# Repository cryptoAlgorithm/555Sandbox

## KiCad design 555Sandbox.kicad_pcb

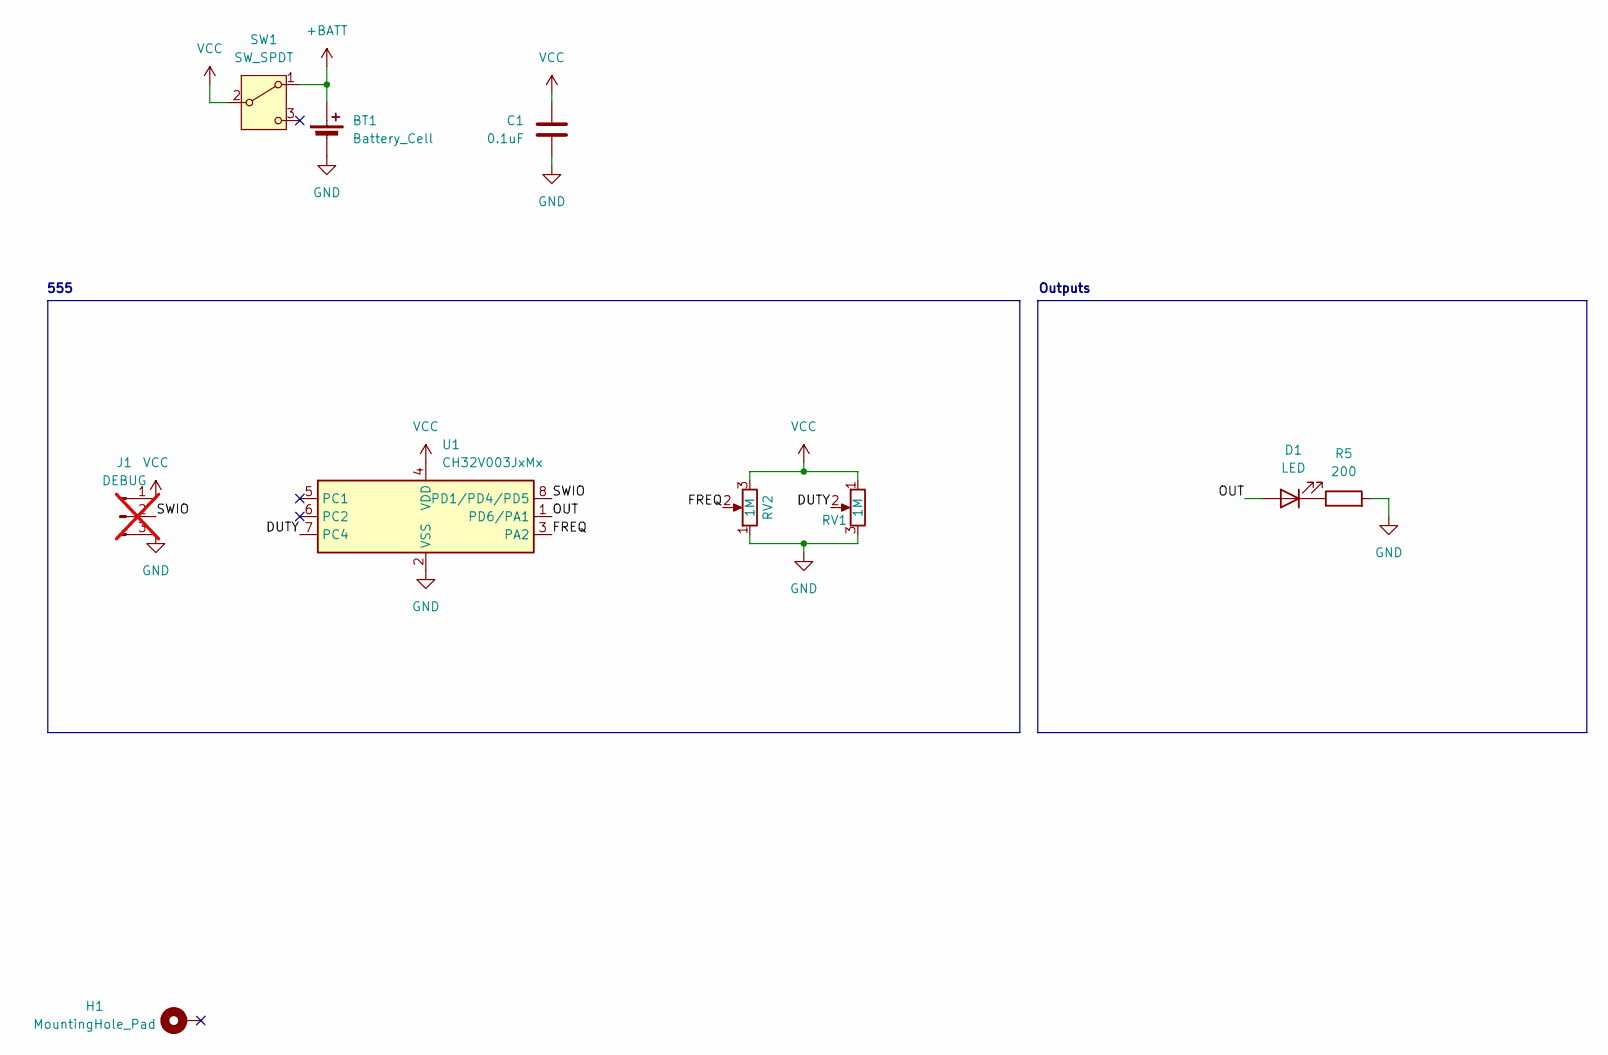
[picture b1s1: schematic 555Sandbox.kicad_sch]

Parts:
BT1: Battery_Cell; BatteryHolder_Keystone_3000_1x12mm; Part C238097
C1: 0.1uF; C_0603_1608Metric; Part C14663
D1: LED; LED_PLCC_2835; Part C7371920
H1: MountingHole_Pad; MountingHole_3mm_Pad
J1: DEBUG; PinHeader_1x03_P1.27mm_Vertical; not fitted
R5: 200; R_0603_1608Metric; Part C8218
RV1, RV2: 1M; Potentiometer_Runtron_RM-065_Vertical
SW1: SW_SPDT; SW_Slide_SPDT_Angled_CK_OS102011MA1Q
U1: CH32V003JxMx; SOP-8_3.9x4.9mm_P1.27mm; Part C5346354

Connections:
+BATT: BT1.1 (+), SW1.1 (A)
/DUTY: RV1.2, U1.7 (PC4)
/FREQ: RV2.2, U1.3 (PA2)
/OUT: D1.2 (A), U1.1 (PD6/PA1)
/SWIO: J1.2, U1.8 (PD1/PD4/PD5)
GND: BT1.2 (-), C1.2, J1.3, R5.2, RV1.3, RV2.1, U1.2 (VSS)
unnamed: D1.1 (K), R5.1
VCC: C1.1, J1.1, RV1.1, RV2.3, SW1.2 (B), U1.4 (VDD)

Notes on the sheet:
Outputs
555

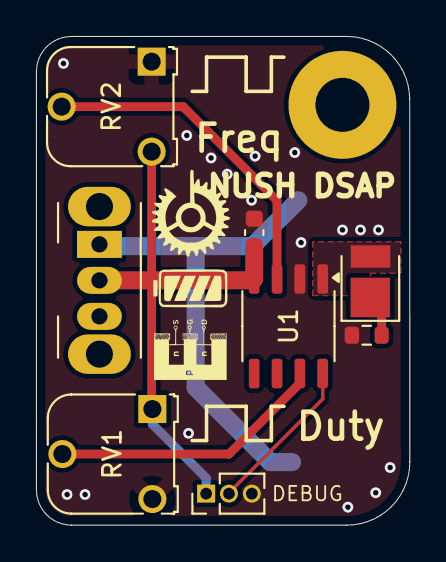
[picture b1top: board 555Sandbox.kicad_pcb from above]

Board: 2 copper layers, 20.7 x 27.1 mm, 10 parts (1 on the bottom side), 8 nets.

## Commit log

2024-04-06 feat: initial commit, v0.1 with configurable on and off time
2024-04-07 fix: mode switch footprint & silkscreen labels
2024-04-10 feat: update with separate freq and period adjustment
2024-04-10 fix: JLC text
2024-04-13 fix: connect trig to cap directly
2024-04-14 patch: silkscreen updates
2024-04-15 patch: back silkscreen logo additions
2024-04-30 fix: polarised capacitor and erronous silkscreen label
2024-05-02 feat: refresh majority of pcb to improve ease of assembly
2024-05-03 patch: minor silkscreen updates
2024-05-04 patch: split resistor into 2, update silkscreen
    allow use of same resistor values instead of an additional 6k7 resistor
2024-05-04 fix: replace missing EIG on silkscreen
2024-07-25 feat: board v1.4
2024-07-26 feat: microcontroller based v2.1
